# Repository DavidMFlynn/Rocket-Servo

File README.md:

# Rocket-Servo
 Altimeter triggered 2 position servo driver

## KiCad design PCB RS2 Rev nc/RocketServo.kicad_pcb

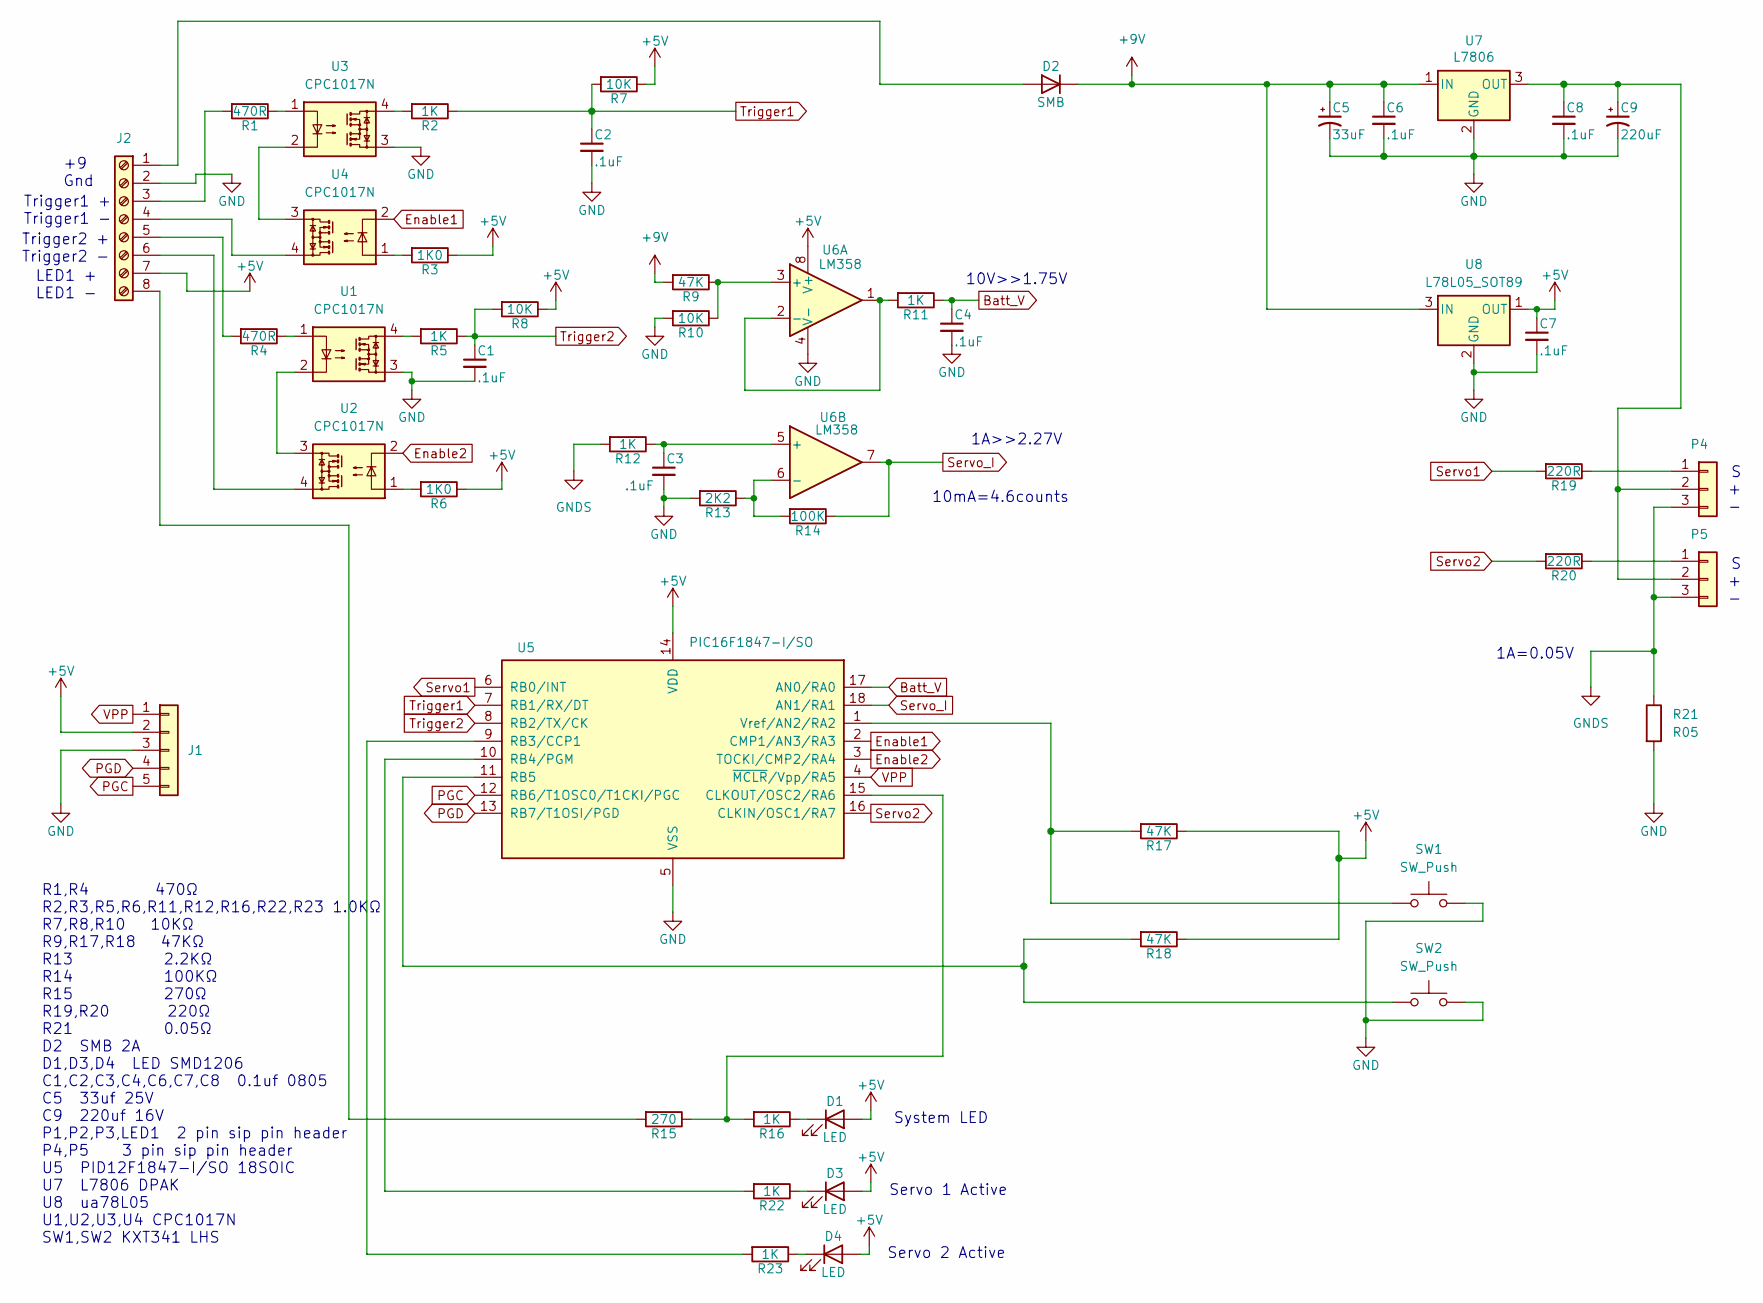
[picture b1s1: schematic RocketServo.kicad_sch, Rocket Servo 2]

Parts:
C1, C2, C3, C4, C6, C7, C8: .1uF; C_0805_2012Metric_Pad1.18x1.45mm_HandSolder
C5: 33uF; CP_Radial_D5.0mm_P2.00mm
C9: 220uF; CP_Radial_D6.3mm_P2.50mm
D1, D3, D4: LED; LED_1206_3216Metric_Pad1.42x1.75mm_HandSolder
D2: SMB; D_SMA
J1: Conn_01x05; PinHeader_1x05_P2.54mm_Vertical
J2: Screw_Terminal_01x08; TerminalBlock_Xinya_XY308-2.54-8P_1x08_P2.54mm_Horizontal
P4, P5: Conn_01x03; PinHeader_1x03_P2.54mm_Vertical
R1, R4: 470R; R_0805_2012Metric_Pad1.20x1.40mm_HandSolder
R2, R5, R11, R12, R16, R22, R23: 1K; R_0805_2012Metric_Pad1.20x1.40mm_HandSolder
R3, R6: 1K0; R_0805_2012Metric_Pad1.20x1.40mm_HandSolder
R7, R8, R10: 10K; R_0805_2012Metric_Pad1.20x1.40mm_HandSolder
R9, R17, R18: 47K; R_0805_2012Metric_Pad1.20x1.40mm_HandSolder
R13: 2K2; R_0805_2012Metric_Pad1.20x1.40mm_HandSolder
R14: 100K; R_0805_2012Metric_Pad1.20x1.40mm_HandSolder
R15: 270; R_0805_2012Metric_Pad1.20x1.40mm_HandSolder
R19, R20: 220R; R_0805_2012Metric_Pad1.20x1.40mm_HandSolder
R21: R05; R_2512_6332Metric_Pad1.40x3.35mm_HandSolder
SW1, SW2: SW_Push; R_1206_3216Metric
U1, U2, U3, U4: CPC1017N; SOP-4_3.8x4.1mm_P2.54mm
U5: PIC16F1847-I/SO; SOIC-18W_7.5x11.6mm_P1.27mm
U6: LM358; SOIC-8_3.9x4.9mm_P1.27mm
U7: L7806; TO-263-2
U8: L78L05_SOT89; SOT-89-3

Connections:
+5V: C7.1, D1.2 (A), D3.2 (A), D4.2 (A), J1.2, J2.7, R3.1, R6.1, R7.1, R8.1, R17.1, R18.1, U5.14 (VDD), U6.8 (V+), U8.1 (OUT)
+9V: C5.1, C6.1, D2.1 (K), R9.2, U7.1 (IN), U8.3 (IN)
Batt_V: C4.1, R11.1, U5.17 (AN0/RA0)
Enable1: U4.2, U5.2 (CMP1/AN3/RA3)
Enable2: U2.2, U5.3 (TOCKI/CMP2/RA4)
GND: C1.2, C2.2, C3.2, C4.2, C5.2, C6.2, C7.2, C8.2, C9.2, J1.3, J2.2, R10.2, R13.2, R21.2, SW1.2, SW2.2, U1.3, U3.3, U5.5 (VSS), U6.4 (V-), U7.2 (GND), U8.2 (GND)
GNDS: P4.3, P5.3, R12.2, R21.1
unnamed: D1.1 (K), R16.1
unnamed: D2.2 (A), J2.1
unnamed: D3.1 (K), R22.1
unnamed: D4.1 (K), R23.1
unnamed: J2.3, R1.2
unnamed: J2.4, U4.4
unnamed: J2.5, R4.2
unnamed: J2.6, U2.4
unnamed: J2.8, R15.2
unnamed: P4.1, R19.1
unnamed: C8.1, C9.1, P4.2, P5.2, U7.3 (OUT)
unnamed: P5.1, R20.1
unnamed: R1.1, U3.1
unnamed: R2.2, U3.4
unnamed: R3.2, U4.1
unnamed: R4.1, U1.1
unnamed: R5.2, U1.4
unnamed: R6.2, U2.1
unnamed: U1.2, U2.3
unnamed: U3.2, U4.3
unnamed: R15.1, R16.2, U5.15 (CLKOUT/OSC2/RA6)
unnamed: R23.2, U5.9 (RB3/CCP1)
unnamed: R22.2, U5.10 (RB4/PGM)
unnamed: R18.2, SW2.1, U5.11 (RB5)
unnamed: R17.2, SW1.1, U5.1 (Vref/AN2/RA2)
unnamed: R9.1, R10.1, U6.3 (+)
unnamed: R11.2, U6.1, U6.2 (-)
unnamed: C3.1, R12.1, U6.5 (+)
unnamed: R13.1, R14.2, U6.6 (-)
PGC: J1.5, U5.12 (RB6/T1OSC0/T1CKI/PGC)
PGD: J1.4, U5.13 (RB7/T1OSI/PGD)
Servo1: R19.2, U5.6 (RB0/INT)
Servo2: R20.2, U5.16 (CLKIN/OSC1/RA7)
Servo_I: R14.1, U5.18 (AN1/RA1), U6.7
Trigger1: C2.1, R2.1, R7.2, U5.7 (RB1/RX/DT)
Trigger2: C1.1, R5.1, R8.2, U5.8 (RB2/TX/CK)
VPP: J1.1, U5.4 (~MCLR/Vpp/RA5)

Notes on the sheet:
+9 Gnd
R1,R4 470Ω R2,R3,R5,R6,R11,R12,R16,R22,R23 1.0KΩ R7,R8,R10 10KΩ R9,R17,R18 47KΩ R13 2.2KΩ R14 100KΩ R15 270Ω R19,R20 220Ω R21 0.05Ω D2 SMB 2A D1,D3,D4 LED SMD1206 C1,C2,C3,C4,C6,C7,C8 0.1uf 0805 C5 33uf 25V C9 220uf 16V P1,P2,P3,LED1 2 pin sip pin header P4,P5 3 pin sip pin header U5 PID12F1847-I/S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
S + -
1A>>2.27V
Servo 2 Active
1A=0.05V
10V>>1.75V
LED1 + LED1 -
Trigger1 + Trigger1 -
Servo 1 Active
10mA=4.6counts
System LED
Trigger2 + Trigger2 -

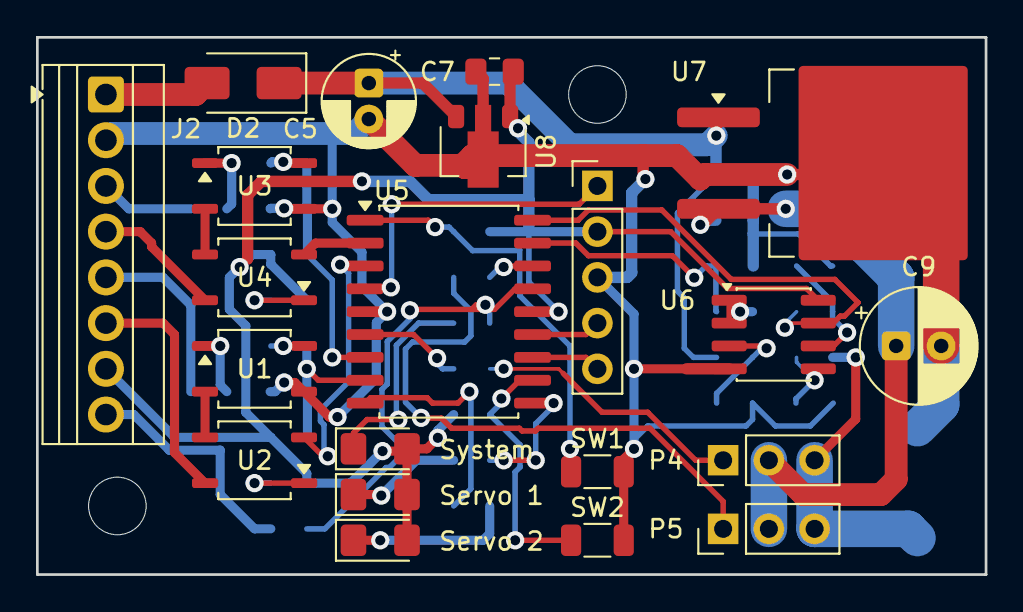
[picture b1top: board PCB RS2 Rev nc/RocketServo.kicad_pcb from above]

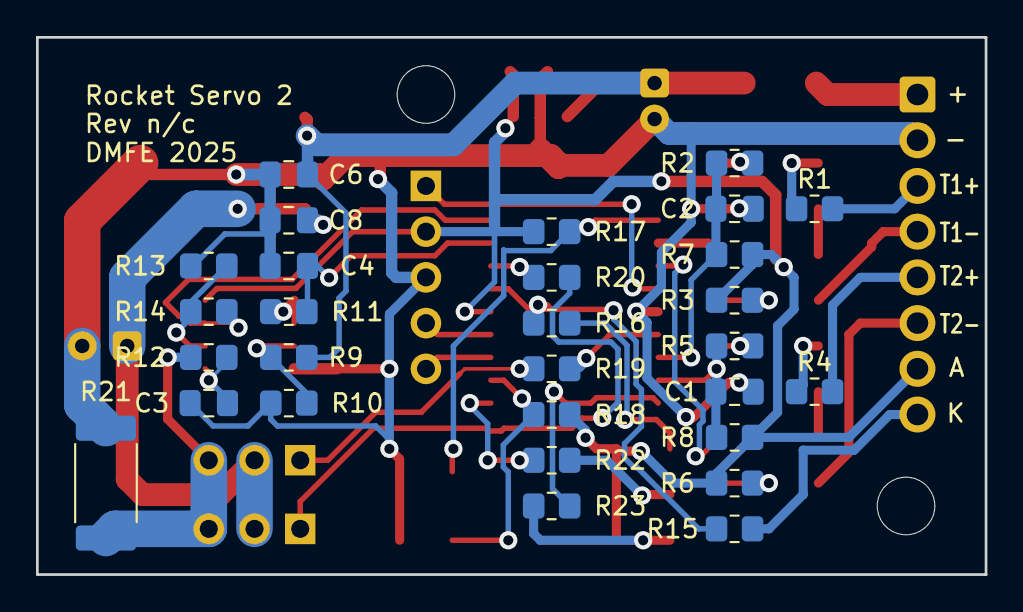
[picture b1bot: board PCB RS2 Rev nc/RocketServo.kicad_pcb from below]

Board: 2 copper layers, 52.7 x 29.8 mm, 52 parts (29 on the bottom side), 44 nets.

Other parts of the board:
H1, H2: MountingHole_3.2mm_M3

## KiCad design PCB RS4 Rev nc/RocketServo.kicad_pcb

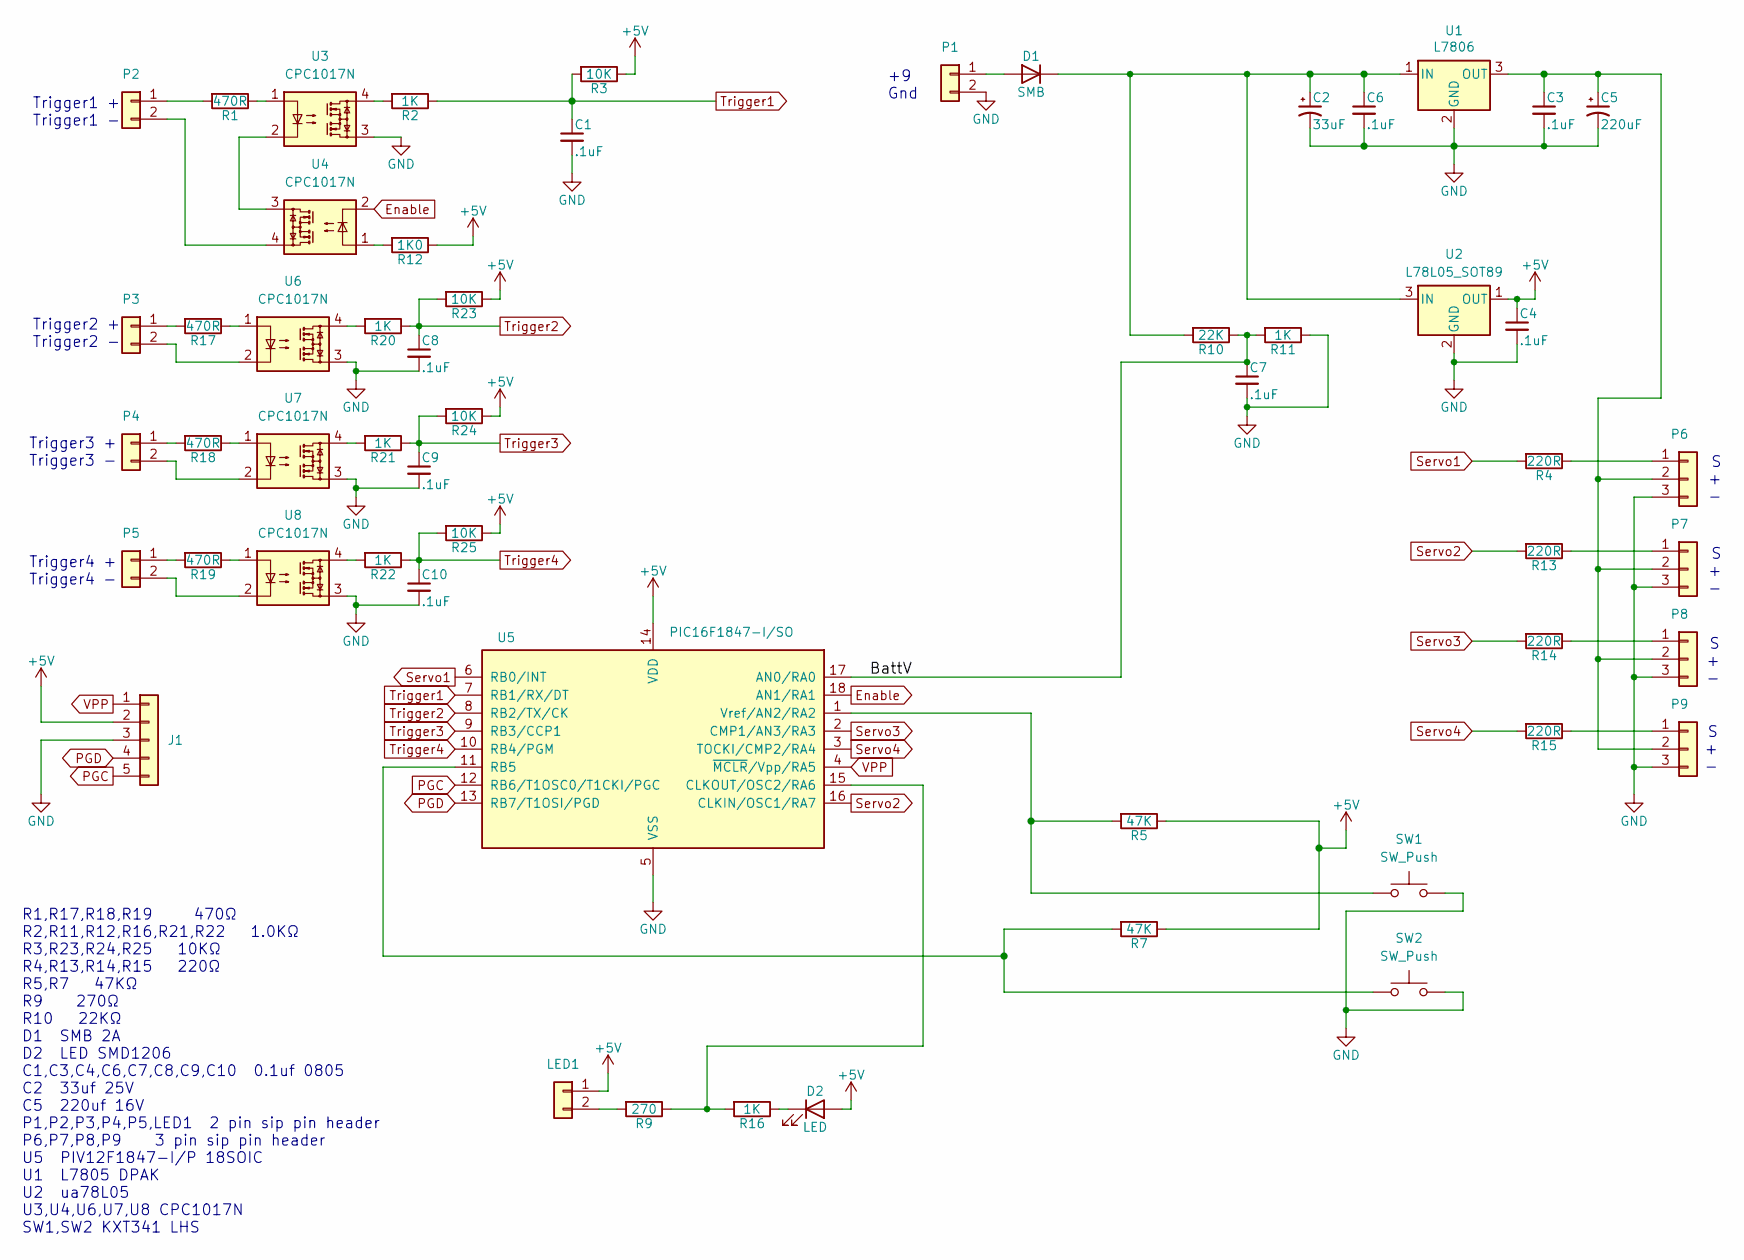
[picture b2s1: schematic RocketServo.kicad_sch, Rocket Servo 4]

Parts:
C1, C3, C4, C6, C7, C8, C9, C10: .1uF; C_0805_2012Metric_Pad1.18x1.45mm_HandSolder
C2: 33uF; CP_Radial_D5.0mm_P2.00mm
C5: 220uF; CP_Radial_D6.3mm_P2.50mm
D1: SMB; D_SMA
D2: LED; LED_1206_3216Metric_Pad1.42x1.75mm_HandSolder
J1: Conn_01x05; PinHeader_1x05_P2.54mm_Vertical
LED1: Conn_01x02; PinHeader_1x02_P2.54mm_Vertical
P1, P2, P3, P4, P5: Conn_01x02; PinHeader_1x02_P2.54mm_Vertical
P6, P7, P8, P9: Conn_01x03; PinHeader_1x03_P2.54mm_Vertical
R1, R17, R18, R19: 470R; R_0805_2012Metric_Pad1.20x1.40mm_HandSolder
R2, R11, R16, R20, R21, R22: 1K; R_0805_2012Metric_Pad1.20x1.40mm_HandSolder
R3, R23, R24, R25: 10K; R_0805_2012Metric_Pad1.20x1.40mm_HandSolder
R4, R13, R14, R15: 220R; R_0805_2012Metric_Pad1.20x1.40mm_HandSolder
R5, R7: 47K; R_0805_2012Metric_Pad1.20x1.40mm_HandSolder
R9: 270; R_0805_2012Metric_Pad1.20x1.40mm_HandSolder
R10: 22K; R_0805_2012Metric_Pad1.20x1.40mm_HandSolder
R12: 1K0; R_0805_2012Metric_Pad1.20x1.40mm_HandSolder
SW1, SW2: SW_Push; R_1206_3216Metric
U1: L7806; TO-263-2
U2: L78L05_SOT89; SOT-89-3
U3, U4, U6, U7, U8: CPC1017N; SOP-4_3.8x4.1mm_P2.54mm
U5: PIC16F1847-I/SO; SOIC-18W_7.5x11.6mm_P1.27mm

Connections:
+5V: C4.1, D2.2 (A), J1.2, LED1.1, R3.1, R5.1, R7.1, R12.1, R23.1, R24.1, R25.1, U2.1 (OUT), U5.14 (VDD)
/BattV: C7.1, R10.1, R11.2, U5.17 (AN0/RA0)
Enable: U4.2, U5.18 (AN1/RA1)
GND: C1.2, C2.2, C3.2, C4.2, C5.2, C6.2, C7.2, C8.2, C9.2, C10.2, J1.3, P1.2, P6.3, P7.3, P8.3, P9.3, R11.1, SW1.2, SW2.2, U1.2 (GND), U2.2 (GND), U3.3, U5.5 (VSS), U6.3, U7.3, U8.3
unnamed: D1.2 (A), P1.1
unnamed: C2.1, C6.1, D1.1 (K), R10.2, U1.1 (IN), U2.3 (IN)
unnamed: D2.1 (K), R16.1
unnamed: LED1.2, R9.2
unnamed: P2.1, R1.2
unnamed: P2.2, U4.4
unnamed: P3.1, R17.2
unnamed: P3.2, U6.2
unnamed: P4.1, R18.2
unnamed: P4.2, U7.2
unnamed: P5.1, R19.2
unnamed: P5.2, U8.2
unnamed: P6.1, R4.1
unnamed: C3.1, C5.1, P6.2, P7.2, P8.2, P9.2, U1.3 (OUT)
unnamed: P7.1, R13.1
unnamed: P8.1, R14.1
unnamed: P9.1, R15.1
unnamed: R1.1, U3.1
unnamed: R2.2, U3.4
unnamed: R12.2, U4.1
unnamed: R17.1, U6.1
unnamed: R18.1, U7.1
unnamed: R19.1, U8.1
unnamed: R20.2, U6.4
unnamed: R21.2, U7.4
unnamed: R22.2, U8.4
unnamed: U3.2, U4.3
unnamed: R9.1, R16.2, U5.15 (CLKOUT/OSC2/RA6)
unnamed: R7.2, SW2.1, U5.11 (RB5)
unnamed: R5.2, SW1.1, U5.1 (Vref/AN2/RA2)
PGC: J1.5, U5.12 (RB6/T1OSC0/T1CKI/PGC)
PGD: J1.4, U5.13 (RB7/T1OSI/PGD)
Servo1: R4.2, U5.6 (RB0/INT)
Servo2: R13.2, U5.16 (CLKIN/OSC1/RA7)
Servo3: R14.2, U5.2 (CMP1/AN3/RA3)
Servo4: R15.2, U5.3 (TOCKI/CMP2/RA4)
Trigger1: C1.1, R2.1, R3.2, U5.7 (RB1/RX/DT)
Trigger2: C8.1, R20.1, R23.2, U5.8 (RB2/TX/CK)
Trigger3: C9.1, R21.1, R24.2, U5.9 (RB3/CCP1)
Trigger4: C10.1, R22.1, R25.2, U5.10 (RB4/PGM)
VPP: J1.1, U5.4 (~MCLR/Vpp/RA5)

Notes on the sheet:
+9 Gnd
Trigger3 + Trigger3 -
R1,R17,R18,R19 470Ω R2,R11,R12,R16,R21,R22 1.0KΩ R3,R23,R24,R25 10KΩ R4,R13,R14,R15 220Ω R5,R7 47KΩ R9 270Ω R10 22KΩ D1 SMB 2A D2 LED SMD1206 C1,C3,C4,C6,C7,C8,C9,C10 0.1uf 0805 C2 33uf 25V C5 220uf 16V P1,P2,P3,P4,P5,LED1 2 pin sip pin header P6,P7,P8,P9 3 pin sip pin header U5 PIV12F1847-I/P 18SO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
S + -
Trigger4 + Trigger4 -
Trigger1 + Trigger1 -
Trigger2 + Trigger2 -

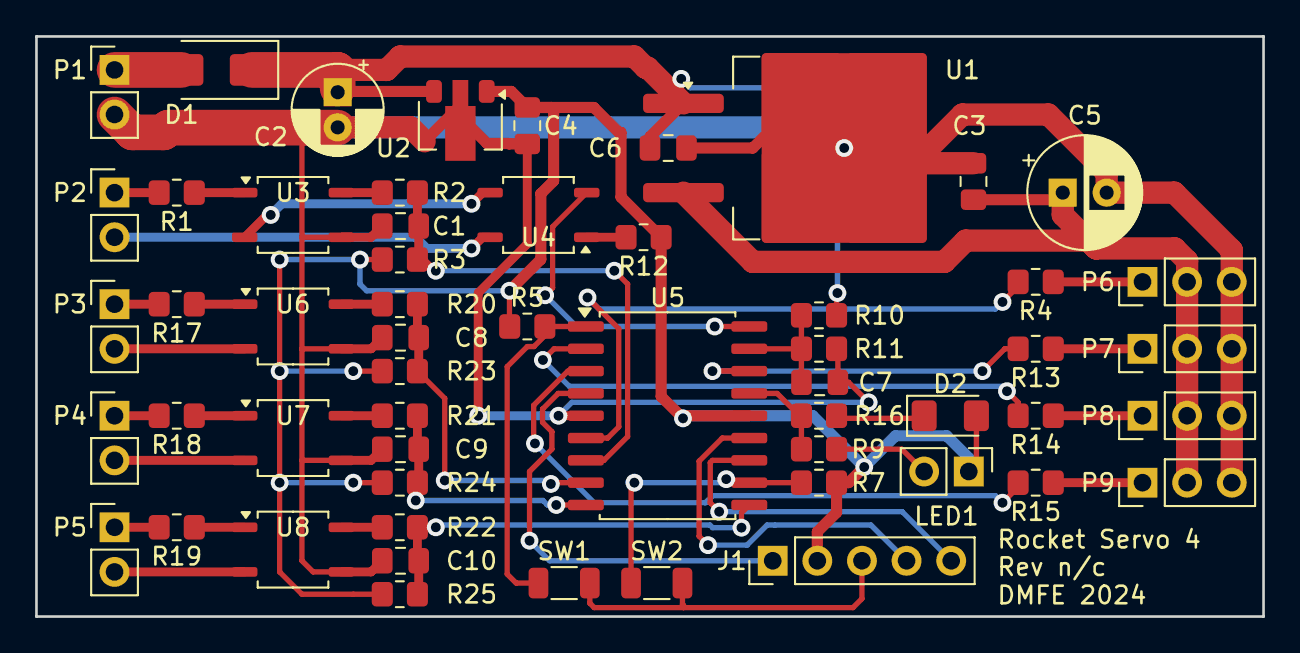
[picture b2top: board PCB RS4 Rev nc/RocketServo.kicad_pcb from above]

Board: 2 copper layers, 69.9 x 33.0 mm, 56 parts (0 on the bottom side), 45 nets.

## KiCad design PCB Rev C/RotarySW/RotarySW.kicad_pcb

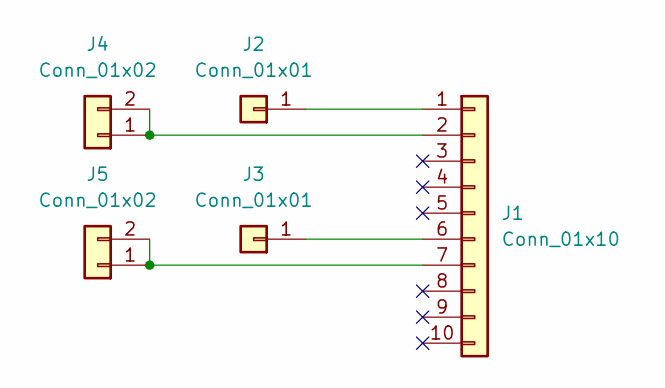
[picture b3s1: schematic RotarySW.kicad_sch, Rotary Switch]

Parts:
J1: Conn_01x10; Rotary2x5
J2, J3: Conn_01x01; PinHeader_1x01_P2.54mm_Vertical
J4, J5: Conn_01x02; PinHeader_1x02_P2.54mm_Vertical

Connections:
unnamed: J1.1, J2.1
unnamed: J1.2, J4.1, J4.2
unnamed: J1.6, J3.1
unnamed: J1.7, J5.1, J5.2

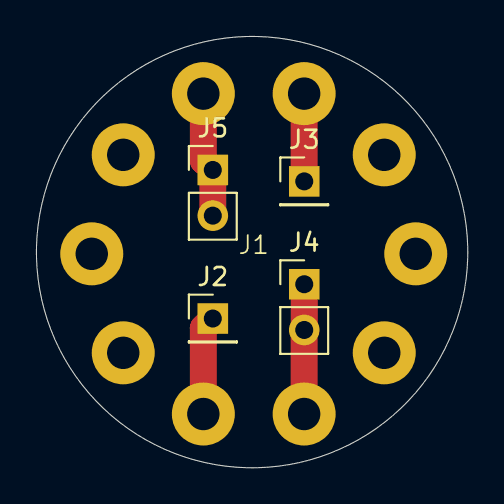
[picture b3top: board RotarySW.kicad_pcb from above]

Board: 2 copper layers, 24.0 x 24.0 mm, 5 parts (0 on the bottom side), 4 nets.

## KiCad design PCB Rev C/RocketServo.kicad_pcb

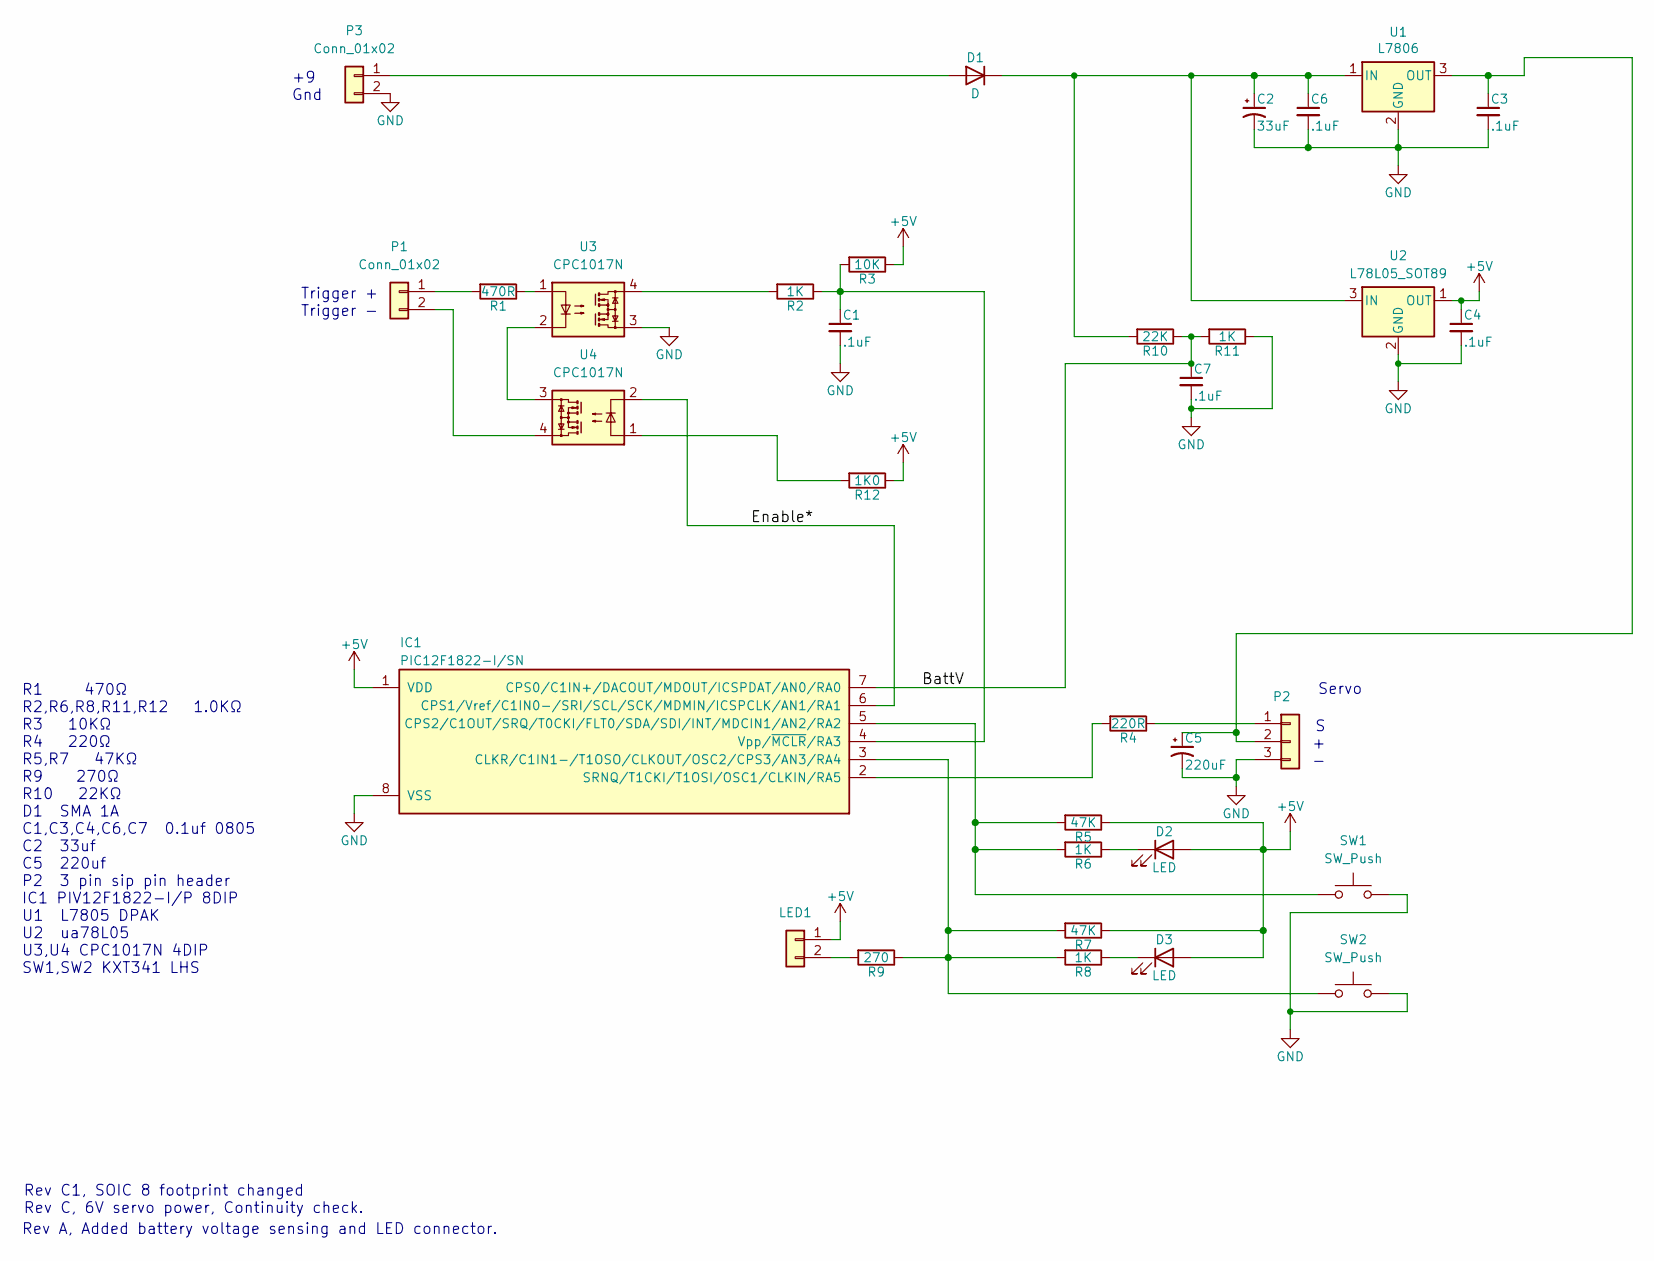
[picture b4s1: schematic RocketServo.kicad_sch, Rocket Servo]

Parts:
C1, C3, C4, C6, C7: .1uF; C_0805_2012Metric_Pad1.18x1.45mm_HandSolder
C2: 33uF; CP_Radial_D5.0mm_P2.00mm
C5: 220uF; CP_Radial_D6.3mm_P2.50mm
D1: D; D_SMA
D2, D3: LED; LED_1206_3216Metric_Pad1.42x1.75mm_HandSolder
IC1: PIC12F1822-I/SN; SOIC-8_3.9x4.9mm_P1.27mm
LED1: Conn_01x02; PinHeader_1x02_P2.54mm_Vertical
P1, P3: Conn_01x02; PinHeader_1x02_P2.54mm_Vertical
P2: Conn_01x03; PinHeader_1x03_P2.54mm_Vertical
R1: 470R; R_0805_2012Metric_Pad1.20x1.40mm_HandSolder
R2, R6, R8, R11: 1K; R_0805_2012Metric_Pad1.20x1.40mm_HandSolder
R3: 10K; R_0805_2012Metric_Pad1.20x1.40mm_HandSolder
R4: 220R; R_0805_2012Metric_Pad1.20x1.40mm_HandSolder
R5, R7: 47K; R_0805_2012Metric_Pad1.20x1.40mm_HandSolder
R9: 270; R_0805_2012Metric_Pad1.20x1.40mm_HandSolder
R10: 22K; R_0805_2012Metric_Pad1.20x1.40mm_HandSolder
R12: 1K0; R_0805_2012Metric_Pad1.20x1.40mm_HandSolder
SW1, SW2: SW_Push; R_1206_3216Metric
U1: L7806; TO-263-2
U2: L78L05_SOT89; SOT-89-3
U3, U4: CPC1017N; SOP-4_3.8x4.1mm_P2.54mm

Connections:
+5V: C4.1, D2.2 (A), D3.2 (A), IC1.1 (VDD), LED1.1, R3.1, R5.1, R7.1, R12.1, U2.1 (OUT)
/BattV: C7.1, IC1.7 (CPS0/C1IN+/DACOUT/MDOUT/ICSPDAT/AN0/RA0), R10.1, R11.2
/Enable*: IC1.6 (CPS1/Vref/C1IN0-/SRI/SCL/SCK/MDMIN/ICSP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), U4.2
GND: C1.2, C2.2, C3.2, C4.2, C5.2, C6.2, C7.2, IC1.8 (VSS), P2.3, P3.2, R11.1, SW1.2, SW2.2, U1.2 (GND), U2.2 (GND), U3.3
unnamed: D1.2 (A), P3.1
unnamed: C2.1, C6.1, D1.1 (K), R10.2, U1.1 (IN), U2.3 (IN)
unnamed: D2.1 (K), R6.1
unnamed: D3.1 (K), R8.1
unnamed: IC1.3 (CLKR/C1IN1-/T1OSO/CLKOUT/OSC2/CPS3/AN3/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), R7.2, R8.2, R9.1, SW2.1
unnamed: IC1.5 (CPS2/C1OUT/SRQ/T0CKI/FLT0/SDA/SDI/INT/M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), R5.2, R6.2, SW1.1
unnamed: IC1.2 (SRNQ/T1CKI/T1OSI/OSC1/CLKIN/RA5), R4.2
unnamed: C1.1, IC1.4 (Vpp/~MCLR/RA3), R2.1, R3.2
unnamed: LED1.2, R9.2
unnamed: P1.1, R1.2
unnamed: P1.2, U4.4
unnamed: P2.1, R4.1
unnamed: C3.1, C5.1, P2.2, U1.3 (OUT)
unnamed: R1.1, U3.1
unnamed: R2.2, U3.4
unnamed: R12.2, U4.1
unnamed: U3.2, U4.3

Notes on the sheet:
+9 Gnd
R1 470Ω R2,R6,R8,R11,R12 1.0KΩ R3 10KΩ R4 220Ω R5,R7 47KΩ R9 270Ω R10 22KΩ D1 SMA 1A C1,C3,C4,C6,C7 0.1uf 0805 C2 33uf C5 220uf P2 3 pin sip pin header IC1 PIV12F1822-I/P 8DIP U1 L7805 DPAK U2 ua78L05 U3,U4 CPC1017N 4DIP SW1,SW2 KXT341 LHS
Rev C1, SOIC 8 footprint changed Rev C, 6V servo power, Continuity check.
Rev A, Added battery voltage sensing and LED connector.
S + -
Trigger + Trigger -
Servo

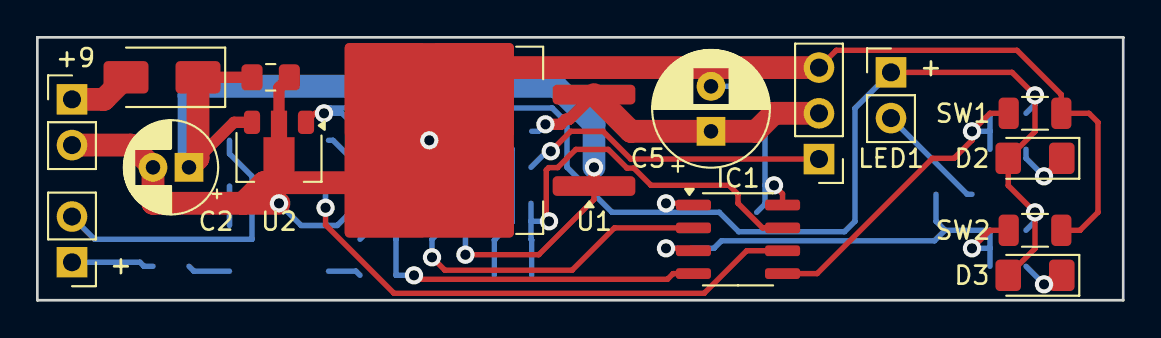
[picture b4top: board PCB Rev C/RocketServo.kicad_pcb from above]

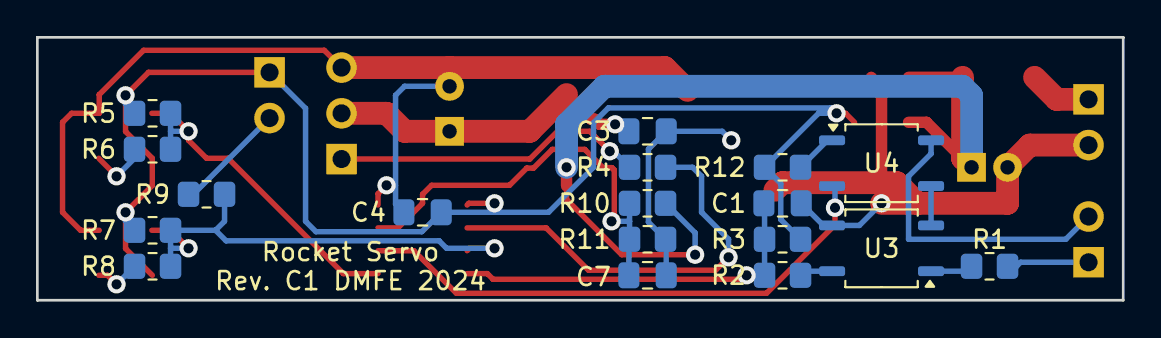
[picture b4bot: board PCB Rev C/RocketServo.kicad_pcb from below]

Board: 2 copper layers, 60.3 x 14.6 mm, 33 parts (18 on the bottom side), 21 nets.

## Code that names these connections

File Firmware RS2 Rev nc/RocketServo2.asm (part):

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;
;====================================================================================================
;
;  Pin 1  RA2 		SW1 Inc switch Active Low Input 
;  Pin 2  RA3 		Enable1 Conductivity Enable Active Low Output	
;  Pin 3  RA4 		Enable2 Conductivity Enable Active Low Output		
;  Pin 4  RA5/MCLR*/Vpp (Input only)	Vpp	
;  Pin 5  VSS (Ground)		Ground
;  Pin 6  RB0/CCP1		Servo1 Signal Output
;  Pin 7  RB1		Trigger1 Active Low Input
;  Pin 8  RB2		Trigger2 Active Low Input
;  Pin 9  RB3		Servo2LED Active Active Low Output
;  Pin 10 RB4		Servo1LED Active Active Low Output
;  Pin 11 RB5		SW2 Dec switch Active Low Input
;  Pin 12 RB6 ICSPCLK		PGC
;  Pin 13 RB7 ICSPDAT		PGD
;  Pin 14 VDD (+5V)		+5V
;  Pin 15 RA6 		System LED Active Low Output
;  Pin 16 RA7/CCP2		Servo2 Signal Output
;  Pin 17 RA0 AN0/Battery (volts-0.5)/21
;  Pin 18 RA1 AN1/Servo_I
;
;====================================================================================================
;
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; INTOSC oscillator: I/O function on CLKIN pin
; WDT disabled
; PWRT disabled
; MCLR/VPP pin function is digital input
; Program memory code protection is disabled
; Data memory code protection is disabled
; Brown-out Reset enabled
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;    Port A bits
PortADDRBits	EQU	b'01100111'
#Define	RA0_In	PORTA,0	;AN0/Battery (volts-0.5)/21
#Define	RA1_In	PORTA,1	;AN1/Servo_I
#Define	IncBtnBit	PORTA,2	;SW1 Inc switch Active Low Input 
#Define	ContEnable1	LATA,3	;Enable1 Conductivity Enable Active Low Output
#Define	ContEnable2	LATA,4	;Enable2 Conductivity Enable Active Low Output
#Define	RA5_In	PORTA,5	; Vpp only
#Define	SystemLED	LATA,6	;Output: 0=LED ON
#Define	SysLEDTrisBit	TRISA,6
#Define	RA7_In	PORTA,7	;CCP2, Servo2
;
PortAValue	EQU	b'00000000'
;
;    Port B bits
PortBDDRBits	EQU	b'11111110'
#Define	RB0_In	PORTB,0	;CCP1, Servo1
#Define	S1CmdInputBit	PORTB,1	;Trigger1 Active Low Input
#Define	S2CmdInputBit	PORTB,2	;Trigger2 Active Low Input
#Define	Servo2LEDBit	PORTB,3	;Servo2LED Active Active Low Output
#Define	Servo2LEDTrisBit	TRISB,3
#Define	Servo1LEDBit	PORTB,4	;Servo1LED Active Active Low Output
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
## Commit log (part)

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2022-09-29 First post
    Waiting for PCB to be made.
2022-11-07 Inverted CMD bit
2022-11-09 Rev A PCB just smaller
2022-12-11 Added LED1 and BattV
2022-12-28 New PCB, blink batt volts
2022-12-28 Added Fab drawings
2023-03-30 Beta 2
2023-04-24 Added parts list to sch
2023-05-04 notes
2023-05-04 Batt V blinking works
2023-08-06 Added Hold mode
2023-08-17 Move Faster
2023-12-06 Update to new kicad
2024-05-12 R10 to 22K
2024-05-13 Assy fixture
2024-09-28 Rev C
    6 volts
2024-10-15 Rev C
    Active enable of arming, 6V servo power
2024-10-18 Rev C1
2024-10-31 Rocket Servo 4 PCB
2025-02-17 fixed some text
2025-02-19 added rotary switch pcb
2025-02-19 moved stuff
2026-01-05 wip 2 ch
2026-04-16 Rocket servo 2
    Firmware not done
2026-04-16 It works
2026-05-11 Soldering fixture
